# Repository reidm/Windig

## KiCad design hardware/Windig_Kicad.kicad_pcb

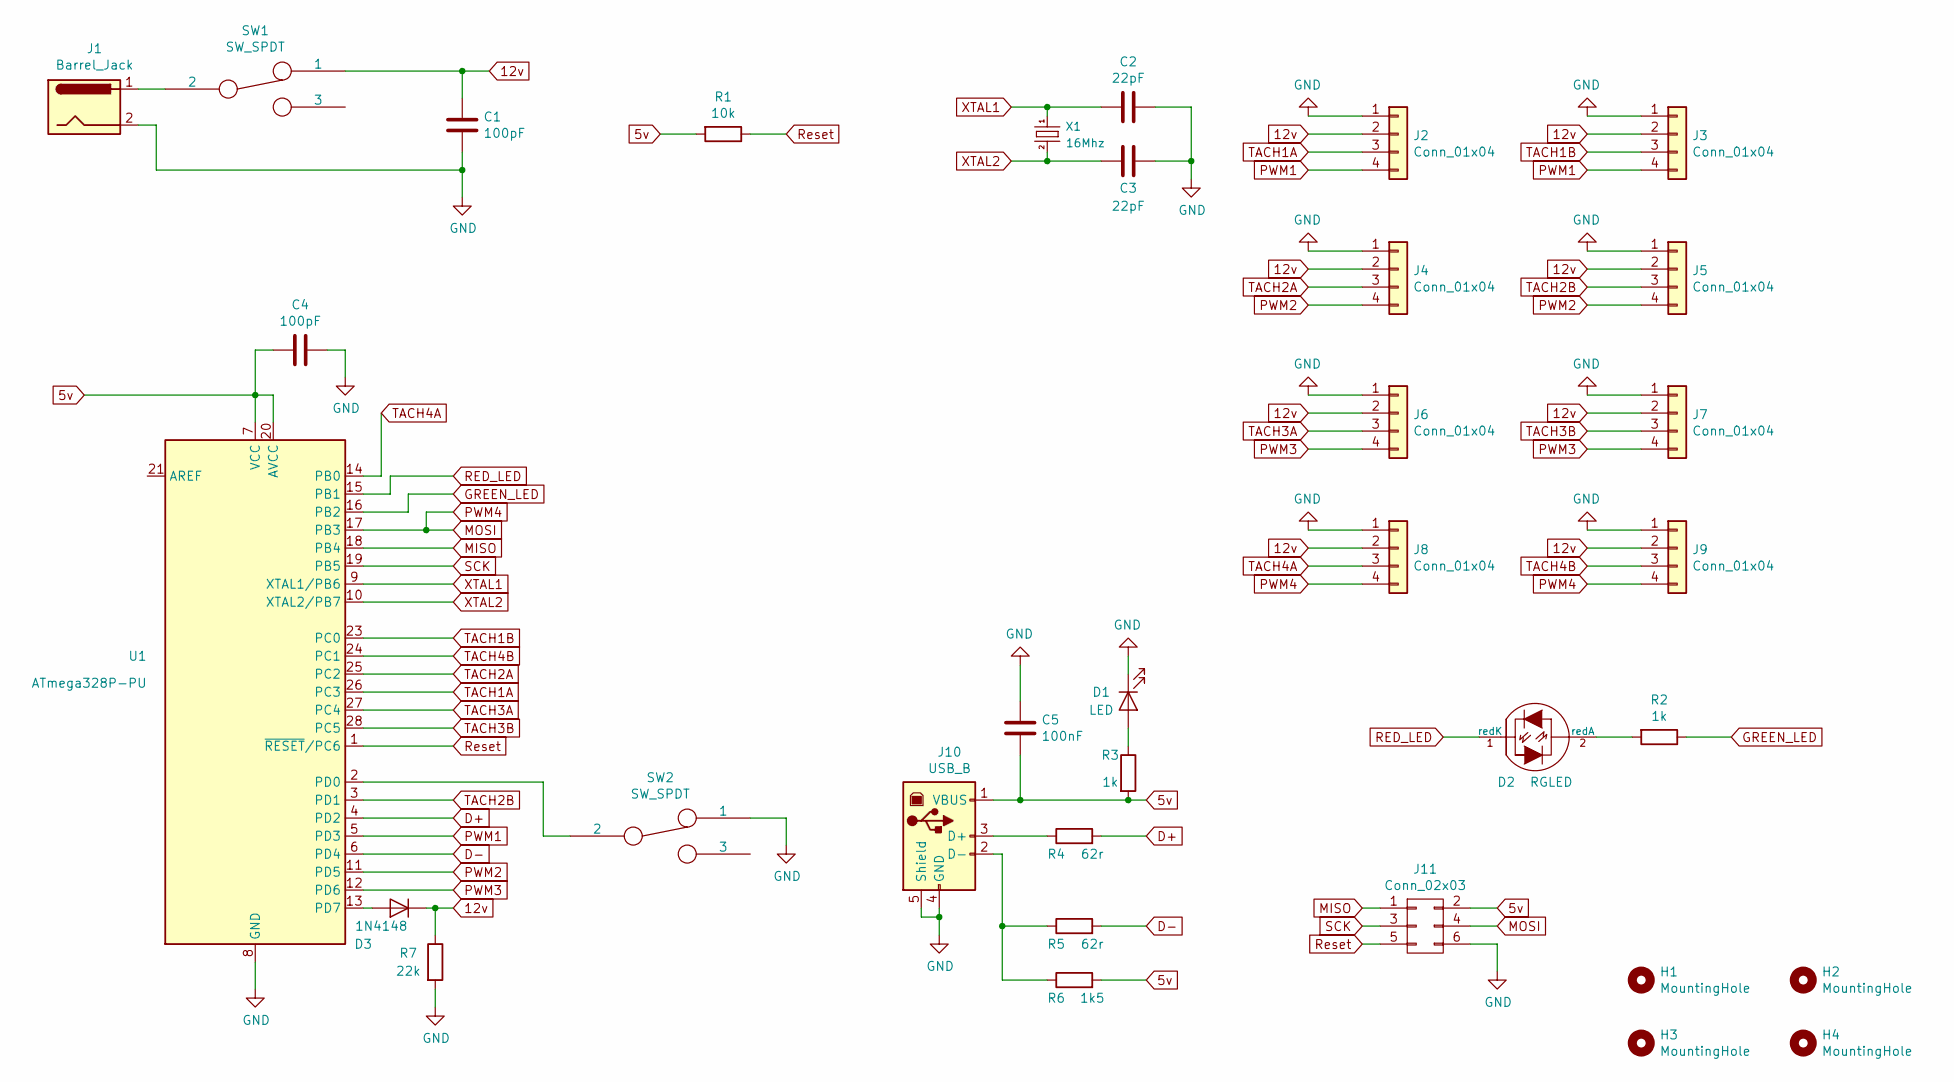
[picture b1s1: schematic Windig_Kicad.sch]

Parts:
C1, C4: 100pF; C_Disc_D3.8mm_W2.6mm_P2.50mm
C2, C3: 22pF; C_Disc_D3.8mm_W2.6mm_P2.50mm
C5: 100nF; C_Disc_D3.8mm_W2.6mm_P2.50mm
D1: LED; LED_D1.8mm_W3.3mm_H2.4mm
D2: RGLED; LED_D1.8mm_W3.3mm_H2.4mm
D3: 1N4148; D_T-1_P5.08mm_Horizontal
H1, H2, H3, H4: MountingHole; MountingHole_3.2mm_M3
J1: Barrel_Jack; BarrelJack_Horizontal
J2, J3, J4, J5, J6, J7, J8, J9: Conn_01x04; Pin_Header_Straight_1x04_Pitch2.54mm
J10: USB_B; USB_B_OST_USB-B1HSxx_Horizontal
J11: Conn_02x03; ISP_Header_2x3_2.54mm_TH
R1: 10k; R_Axial_DIN0207_L6.3mm_D2.5mm_P7.62mm_Horizontal
R2, R3: 1k; R_Axial_DIN0309_L9.0mm_D3.2mm_P2.54mm_Vertical
R4, R5: 62r; R_Axial_DIN0309_L9.0mm_D3.2mm_P2.54mm_Vertical
R6: 1k5; R_Axial_DIN0309_L9.0mm_D3.2mm_P2.54mm_Vertical
R7: 22k; R_Axial_DIN0309_L9.0mm_D3.2mm_P2.54mm_Vertical
SW1, SW2: SW_SPDT; SPDT_KIT
U1: ATmega328P-PU; DIP-28_W7.62mm
X1: 16Mhz; Crystal_16MHz_THT_2.54mm

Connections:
5v: C4.2, C5.2, J10.1 (VBUS), J11.2 (+12V), R1.2, R3.2, R6.2, U1.7 (VCC), U1.20 (AVCC)
12v: C1.1, D3.1 (K), J2.2, J3.2, J4.2, J5.2, J6.2, J7.2, J8.2, J9.2, R7.1, SW1.1
D+: R4.2, U1.4 (PD2)
D-: R5.2, U1.6 (PD4)
GND: C1.2, C2.1, C3.1, C4.1, C5.1, D1.1 (K), J1.2, J2.1, J3.1, J4.1, J5.1, J6.1, J7.1, J8.1, J9.1, J10.4 (GND), J10.5 (Shield), J11.6 (GND), R7.2, SW2.1, U1.8 (GND), U1.22 (GND)
GREEN_LED: R2.1, U1.16 (PB2)
MISO: J11.1 (+12V), U1.18 (PB4)
MOSI: J8.4, J9.4, J11.4 (GND), U1.17 (PB3)
unnamed: D1.2 (A), R3.1
unnamed: D2.2 (redA), R2.2
unnamed: D3.2 (A), U1.13 (PD7)
unnamed: J1.1, SW1.2
unnamed: J10.2 (D-), R5.1, R6.1
unnamed: J10.3 (D+), R4.1
unnamed: SW2.2, U1.2 (PD0)
PWM1: J2.4, J3.4, U1.5 (PD3)
PWM2: J4.4, J5.4, U1.11 (PD5)
PWM3: J6.4, J7.4, U1.12 (PD6)
RED_LED: D2.1 (redK), U1.15 (PB1)
Reset: J11.5 (GND), R1.1, U1.1 (~RESET~/PC6)
SCK: J11.3 (GND), U1.19 (PB5)
TACH1A: J2.3, U1.26 (PC3)
TACH1B: J3.3, U1.23 (PC0)
TACH2A: J4.3, U1.25 (PC2)
TACH2B: J5.3, U1.3 (PD1)
TACH3A: J6.3, U1.27 (PC4)
TACH3B: J7.3, U1.28 (PC5)
TACH4A: J8.3, U1.14 (PB0)
TACH4B: J9.3, U1.24 (PC1)
XTAL1: C2.2, U1.9 (XTAL1/PB6), X1.1
XTAL2: C3.2, U1.10 (XTAL2/PB7), X1.2

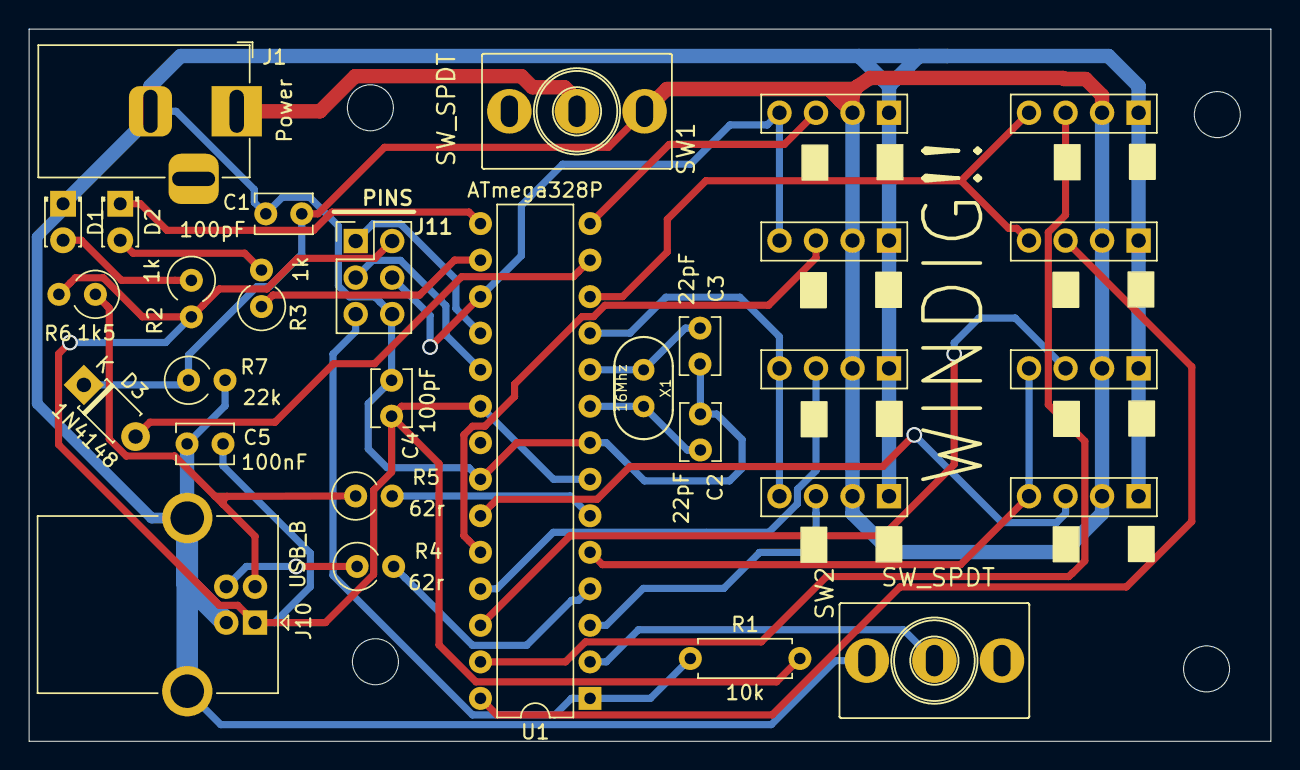
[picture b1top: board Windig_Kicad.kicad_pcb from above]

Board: 2 copper layers, 86.4 x 49.5 mm, 34 parts (1 on the bottom side), 31 nets.

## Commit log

2020-01-03 Initial hardware sketch
2020-01-04 Rough component placemunt update
2020-01-04 Initial board routings
2020-01-10 Component silks complete. Just add art!
2020-01-19 Initial gerber files
2020-01-19 Refilled zones
2020-01-26 Initial gerber zip file
2020-01-26 rename
